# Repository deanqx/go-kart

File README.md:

# JCS-BK_1091_GO-KART_Blinker_Lenkrad_Anzeige

Die gesamte Dokumentation befindet sich unter `docs/pdf/JCS-BK_1091_GO-KART_Blinker_Lenkrad_Anzeige_Dokumentation_DeanS.pdf` gefunden werden.

# Abstract

For several years, students at the technical high school have been working on upgrading a go-kart by
integrating systems typically found in modern cars. The individual modules communicate via a CAN
bus network, similar to that used in real vehicles. Two microcontrollers from the AVR family are used
throughout the system. The task is devided into multiple projects − one for each student.
This document describes the development of the light modules and the cockpit module. There is also a
video showcasing the development. The lighting system consists of four modules, one for each corner
of the vehicle. The two front modules support upper beam, lower beam, and daytime running lights,
while the two rear modules provide tail, brake, and reverse lights.
The cockpit module includes a display, a horn, and several buttons mounted on the steering wheel. It
serves as the central interface between the driver and the vehicle systems. The display presents
information such as speed, battery charge, current gear, light status, and other relevant data. Using the
steering wheel buttons and switches, the driver can control things like the driving direction, light
mode, blinker direction, horn and gear.
All required tasks of this project were successfully completed. The service provider (TIO) did not
finish the Java-based frontend; however, the serial communication interface has already been
implemented. Since the other projects have not yet integrated CAN bus communication into their
modules, communication between the cockpit and the other systems is currently not possible. In
addition, a 3D-printed case for the display and caps for the buttons could be developed in the future.

# Kurzfassung

Seit mehreren Jahren arbeiten Schüler der gymnasialen Oberstufe Bereich Technik daran, ein Go-Kart
durch die Integration von Systemen, die typischerweise in modernen Autos zu finden sind,
aufzurüsten. Die einzelnen Module kommunizieren über CAN-Bus, ähnlich wie es in echten
Fahrzeugen verwendet wird. Im gesamten System kommen zwei Mikrocontroller aus der AVR-Familie
zum Einsatz. Die Aufgabe ist in mehrere Projekte unterteilt – eines für jeden Schüler.
Dieses Dokument beschreibt die Entwicklung der Lichtanlage, des Lenkrads und der Tachoanzeige.
Des weiteren gibt es ein Video in dem die Entwicklung gezeigt wird. Die Lichtanlage besteht aus vier
Modulen, eines für jede Ecke des Fahrzeugs. Die beiden vorderen Module unterstützen Fernlicht,
Abblendlicht und Tagfahrlicht, während die beiden hinteren Module Rücklicht, Bremslicht und
Rückfahrlicht liefern.
Das Cockpitmodul umfasst ein Display, eine Hupe und mehrere am Lenkrad angebrachte Taster. Es
dient als zentrale Schnittstelle zwischen dem Fahrer und den Fahrzeugsystemen. Das Display zeigt
Informationen wie Geschwindigkeit, Batterieladestand, aktueller Gang, Lichtstatus und andere
relevante Daten an. Mit den Tasten und Schaltern am Lenkrad kann der Fahrer beispielsweise die
Fahrtrichtung, den Lichtmodus, die Blinkerrichtung, die Hupe und den Gang steuern.
Alle gegebenen Aufgaben dieses Projekts wurden erfolgreich abgeschlossen. Der Dienstleister (TIO)
hat das Java-basierte Frontend nicht fertiggestellt, jedoch wurde die serielle Schnittstelle bereits
implementiert. Da die anderen Projekte die CAN-Bus-Kommunikation noch nicht in ihre Module
integriert haben, ist eine Kommunikation zwischen dem Cockpit und den anderen Systemen derzeit
nicht möglich. Darüber hinaus könnte in Zukunft ein 3D-gedrucktes Gehäuse für das Cockpit und
Kappen für die Lenkrad-Taster entwickelt werden.

# Credits

Dieses Projekt verwendet AVR-Bibliotheken, darunter:

- Eine verbesserte Version von [dergraaf/avr-can-lib](https://github.com/dergraaf/avr-can-lib)
  welche auf den ATmega16M1 angepasst wurde.
- USART Bibliothek [jnk0le/AVR-UART-lib](https://github.com/jnk0le/AVR-UART-lib)

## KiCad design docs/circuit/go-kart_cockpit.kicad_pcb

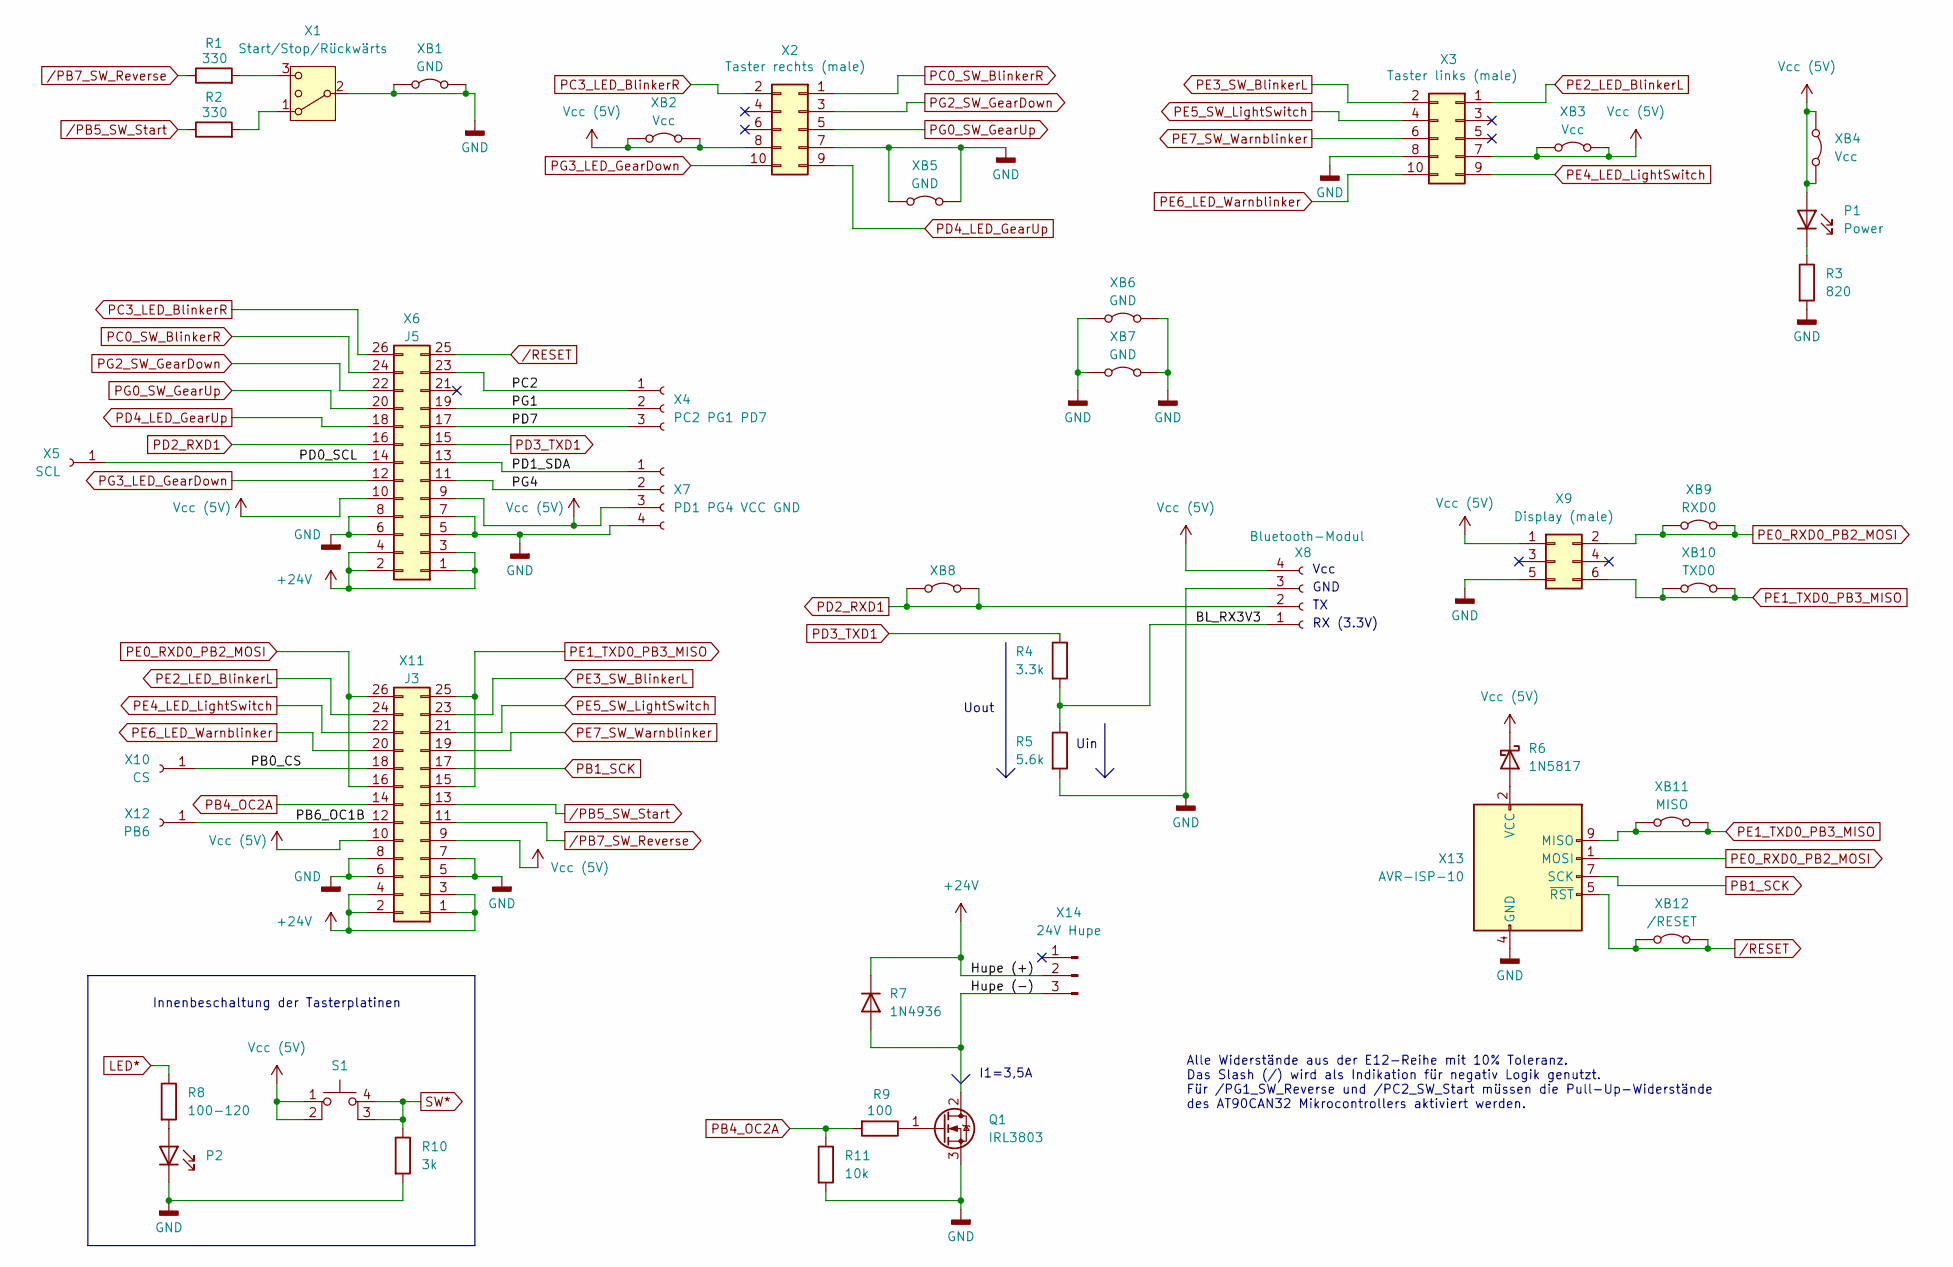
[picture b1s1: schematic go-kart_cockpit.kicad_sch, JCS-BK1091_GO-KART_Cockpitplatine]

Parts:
P1, P2: Power; LED_D3.0mm_Horizontal_O1.27mm_Z6.0mm
Q1: IRL3803; TO-220F-3_Horizontal_TabDown
R1, R2: 330; R_Axial_DIN0207_L6.3mm_D2.5mm_P10.16mm_Horizontal
R3: 820; R_Axial_DIN0309_L9.0mm_D3.2mm_P12.70mm_Horizontal
R4: 3.3k; R_Axial_DIN0207_L6.3mm_D2.5mm_P10.16mm_Horizontal
R5: 5.6k; R_Axial_DIN0207_L6.3mm_D2.5mm_P10.16mm_Horizontal
R6: 1N5817; D_DO-41_SOD81_P10.16mm_Horizontal
R7: 1N4936; D_DO-41_SOD81_P10.16mm_Horizontal
R8: 100-120
R9: 100; R_Axial_DIN0207_L6.3mm_D2.5mm_P7.62mm_Horizontal
R10: 3k
R11: 10k; R_Axial_DIN0207_L6.3mm_D2.5mm_P7.62mm_Horizontal
S1: SW_MEC_5E
X1: Start/Stop/Rückwärts; PhoenixContact_MC_1,5_3-G-5.08_1x03_P5.08mm_Horizontal
X2: Taster rechts (male); IDC-Header_2x05_P2.54mm_Horizontal
X3: Taster links (male); IDC-Header_2x05_P2.54mm_Horizontal
X4: PC2 PG1 PD7; PinSocket_1x03_P2.54mm_Vertical
X5: SCL; PinSocket_1x01_P2.54mm_Vertical
X6: J5; PinSocket_2x13_P2.54mm_Vertical
X7: PD1 PG4 VCC GND; PinSocket_1x04_P2.54mm_Vertical
X8: Bluetooth-Modul; PinSocket_1x04_P2.54mm_Horizontal
X9: Display (male); IDC-Header_2x03_P2.54mm_Horizontal
X10: CS; PinSocket_1x01_P2.54mm_Vertical
X11: J3; PinSocket_2x13_P2.54mm_Vertical
X12: PB6; PinSocket_1x01_P2.54mm_Vertical
X13: AVR-ISP-10; IDC-Header_2x05_P2.54mm_Horizontal
X14: 24V Hupe; PhoenixContact_MC_1,5_3-G-5.08_1x03_P5.08mm_Horizontal
XB1, XB6: GND; R_Axial_DIN0207_L6.3mm_D2.5mm_P10.16mm_Horizontal
XB2, XB3: Vcc; R_Axial_DIN0207_L6.3mm_D2.5mm_P10.16mm_Horizontal
XB4: Vcc; R_Axial_DIN0207_L6.3mm_D2.5mm_P7.62mm_Horizontal
XB5: GND; R_Axial_DIN0207_L6.3mm_D2.5mm_P15.24mm_Horizontal
XB7: GND; R_Axial_DIN0207_L6.3mm_D2.5mm_P7.62mm_Horizontal
XB8: R_Axial_DIN0207_L6.3mm_D2.5mm_P15.24mm_Horizontal
XB9: RXD0; R_Axial_DIN0207_L6.3mm_D2.5mm_P10.16mm_Horizontal
XB10: TXD0; R_Axial_DIN0207_L6.3mm_D2.5mm_P10.16mm_Horizontal
XB11: MISO; TestPoint_2Pads_Pitch5.08mm_Drill1.3mm
XB12: /RESET; R_Axial_DIN0207_L6.3mm_D2.5mm_P15.24mm_Horizontal

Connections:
+24V: R7.1 (K), X6.1, X6.2, X6.3, X6.4, X11.1, X11.2, X11.3, X11.4, X14.2
/BL_RX3V3: R4.2, R5.1, X8.1
/Hupe (-): Q1.2 (D), R7.2 (A), X14.3
/PB0_CS: X10.1, X11.18
/PB6_OC1B: X11.12, X12.1
/PC2: X4.1, X6.23
/PD0_SCL: X5.1, X6.14
/PD1_SDA: X6.13, X7.1
/PD7: X4.3, X6.17
/PG1: X4.2, X6.19
/PG4: X6.11, X7.2
GND: P2.1 (K), Q1.3 (S), R3.2, R5.2, R10.2, R11.2, X1.2 (3), X2.7, X3.8, X6.5, X6.6, X6.7, X6.8, X7.4, X8.3, X9.5, X11.5, X11.6, X11.7, X11.8, X13.4 (GND), X13.6 (GND), X13.8 (GND), X13.10 (GND), XB1.1 (A), XB1.2 (B), XB5.1 (A), XB5.2 (B), XB6.1 (A), XB6.2 (B), XB7.1 (A), XB7.2 (B)
unnamed: P1.1 (K), R3.1
unnamed: P2.2 (A), R8.2
unnamed: Q1.1 (G), R9.1
unnamed: R2.2, X1.1
unnamed: R6.2 (A), X13.2 (VCC)
unnamed: R10.1, S1.3 (K), S1.4 (A)
unnamed: R1.2, X1.3 (4)
PB1_SCK: X11.17, X13.7 (SCK)
PB4_OC2A: R9.2, R11.1, X11.14
PC0_SW_BlinkerR: X2.1, X6.24
PC3_LED_BlinkerR: X2.2, X6.26
PD2_RXD1: X6.16, X8.2, XB8.1 (A), XB8.2 (B)
PD3_TXD1: R4.1, X6.15
PD4_LED_GearUp: X2.9, X6.18
PE0_RXD0_PB2_MOSI: X9.2, X11.16, X11.26, X13.1 (MOSI), XB9.1 (A), XB9.2 (B)
PE1_TXD0_PB3_MISO: X9.6, X11.15, X11.25, X13.9 (MISO), XB10.1 (A), XB10.2 (B), XB11.1 (A), XB11.2 (B)
PE2_LED_BlinkerL: X3.1, X11.24
PE3_SW_BlinkerL: X3.2, X11.23
PE4_LED_LightSwitch: X3.9, X11.22
PE5_SW_LightSwitch: X3.4, X11.21
PE6_LED_Warnblinker: X3.10, X11.20
PE7_SW_Warnblinker: X3.6, X11.19
PG0_SW_GearUp: X2.5, X6.20
PG2_SW_GearDown: X2.3, X6.22
PG3_LED_GearDown: X2.10, X6.12
Vcc (5V): P1.2 (A), R6.1 (K), S1.1, S1.2, X2.8, X3.7, X6.9, X6.10, X7.3, X8.4, X9.1, X11.9, X11.10, XB2.1 (A), XB2.2 (B), XB3.1 (A), XB3.2 (B), XB4.1 (A), XB4.2 (B)
/PB5_SW_Start: R2.1, X11.13
/PB7_SW_Reverse: R1.1, X11.11
/RESET: X6.25, X13.5 (~RST), XB12.1 (A), XB12.2 (B)

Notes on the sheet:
Innenbeschaltung der Tasterplatinen
Uin
Alle Widerstände aus der E12-Reihe mit 10% Toleranz. Das Slash (/) wird als Indikation für negativ Logik genutzt. Für /PG1_SW_Reverse und /PC2_SW_Start müssen die Pull-Up-Widerstände des AT90CAN32 Mikrocontrollers aktiviert werden.
I1=3,5A
GND
Vcc
Uout
RX (3.3V)

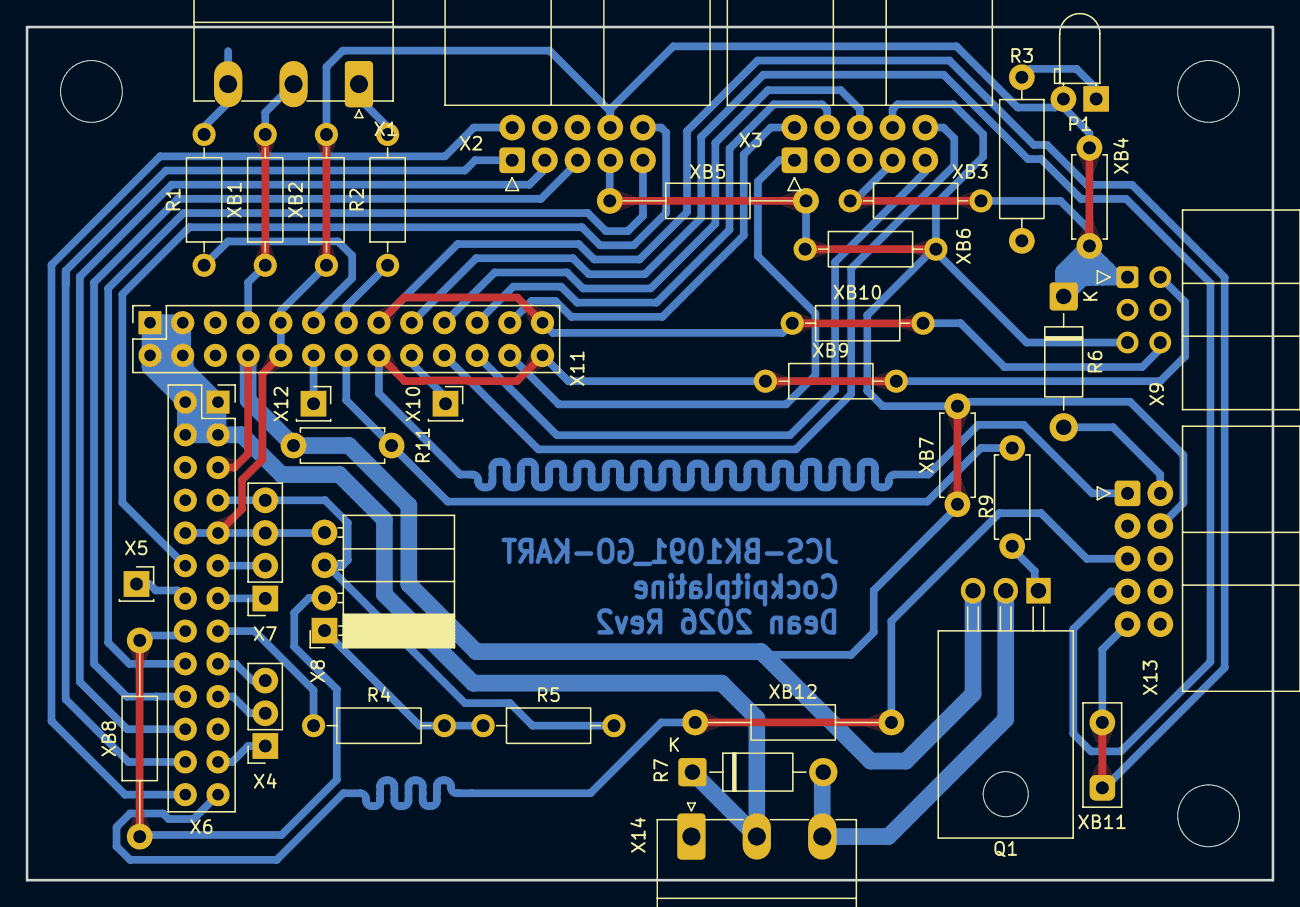
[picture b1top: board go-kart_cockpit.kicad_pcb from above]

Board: 2 copper layers, 96.8 x 66.2 mm, 37 parts (0 on the bottom side), 39 nets.

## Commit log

2025-09-08 feat: setup docs format
2025-09-11 docs: rename docs to documentation
2025-09-12 feat(pflichtenheft): add first page and rough layout
2025-09-22 feat: insert lastenheft into pflichtenheft
2025-09-22 feat: add projects of predecessors, add goals and existing things
2025-09-25 fix: link and Deckblatt
2025-09-25 fix: remove lock
2025-09-25 feat(pflichtenheft): Terminplan eingefügt
2025-09-26 feat(pflichtenheft): change structure and insert missing tables
2025-09-26 feat(pflichtenheft): insert title image
2025-09-26 feat(pflichtenheft): first Aufgabenstellung
2025-09-26 feat: improve overall and Aufgabenstellung
2025-09-27 feat: Aufgabenstellung und alte Projekte
2025-09-28 docs(Plichtenheft): erste Abgabe ohne Überarbeitung
2025-09-28 docs(Plichtenheft): erste Abgabe
2025-09-28 docs(Plichtenheft): update all references
2025-10-08 feat: Pflichtenheft Korrektur
2025-11-09 feat: bluetooth module
2025-11-10 feat: test display
2025-11-11 feat: add Spannungsregler
2025-11-12 feat: use block text and hint where to find AT90CAN docs
2025-11-13 feat: trying to upload to AT90CAN32
2025-11-14 feat: blink test for AT90CAN, docs are not complete
2025-11-15 docs: permissions for USB, improved docs for first test with AT90CAN
2025-11-30 feat: final touches on documentation for draft 1
2025-11-30 feat: adjust for Zwischenstand submission
2026-01-19 feat: cockpit display library (untested)
2026-01-20 docs: Schaltplan für Bluetooth, cmake Erklärung, CAN-Sniffing
2026-01-22 docs: images from old projects are not allowed
2026-01-22 docs: general improvements
2026-01-22 docs: sort alte projekte in descending order
2026-01-22 docs: abstract, cockpit-display, oled-display, general improvements
2026-01-23 feat: blink test for ATmega16M1 (blinker module)
2026-01-23 feat: add can library
2026-01-23 docs: cockpit display commands, basic mcu introduction and more
2026-01-23 docs: draft 2 documentation, add Tagesziele
2026-01-24 feat: test LEDs of blinker module
2026-01-24 WIP(blinker): set up can bus
2026-01-27 WIP: trying to use USART on AT90CAN
2026-01-28 build: improve cmake target selection
2026-01-28 fix: usart library for AT90CAN32
2026-01-28 feat: test cockpit display with AT90CAN32, fix cockpit display library
2026-01-29 docs: USB Rechte kurz beschrieben
2026-01-29 docs: small improvement in error message
2026-01-29 WIP: testing CAN on AT90CAN
2026-01-29 WIP: transmitting working, still cant receive
2026-01-30 feat: successful CAN-Bus test with AT90CAN
2026-02-01 feat: successful CAN-Bus echo test with ATmega16M1
2026-02-01 feat: blinker controller
2026-02-03 docs: add Quellenverzeichnis, improve Signaltime diagram
2026-02-04 refactor: move can library to forked repo
2026-02-04 feat: (untested) add commands, add UART for ATmega16M1
2026-02-09 style: reformat uart_AM16M1.h
2026-02-09 feat: control blinker with UART (with bug)
2026-02-09 feat: PWM for break and backlight, send periodically state over CAN
2026-02-10 fix: PWM was not fast enough, Blinker-Modul is working
2026-02-10 build: update cmake and refactore code to support multiple blinker compile targets
2026-02-10 docs: create CAN ID table
2026-02-11 fix: do not send light state if UART command failed
2026-02-11 feat: CAN_ID table first version
2026-02-12 feat(blinker): use correct CAN IDs and state message
2026-02-12 fix(blinker): lower light is turned off by blinker code
2026-02-12 feat: circuit for switches
2026-02-12 WIP: planning cockpit pins
2026-02-12 WIP: circuit
2026-02-12 feat(circuit): use internal pull up resistors
2026-02-13 feat: circuit before rework with larger plate
2026-02-15 feat: planned connections to MCU
2026-02-15 feat: allow disabling upper light
2026-02-15 feat: set pins in code
2026-02-15 feat: cockpit test code (untested)
2026-02-15 feat: TI_Zwischenabgabe
2026-02-16 feat: first sketch of PCB
2026-02-16 feat(circuit): fixed DRC
2026-02-16 feat(circuit): final touches
2026-02-16 feat(PCB): checklist and LED calculation
2026-02-16 feat(PCB): add pull down resistor in preperation for FET
2026-02-16 feat(PCB): add teardrops
2026-02-17 feat(PCB): improve connectors and position
2026-02-17 feat(PCB): replace TIP120 with MOSFET
2026-02-20 feat: cleanup Tasterinnenbeschaltung for presentation
2026-03-02 feat: rework of PCB, fix wrong connection
2026-03-03 feat(PCB): replace 100 ohm preresistors with 330
2026-03-03 fix(PCB): green connector drill holes are too small, built PCB
2026-03-03 feat(cockpit): update hal to reflect PCB change
2026-03-04 WIP(cockpit): test PCB
2026-03-05 feat(cockpit): test program for horn
2026-03-05 feat(cockpit): test all switches
2026-03-05 feat(cockpit): read switches with interrupt
2026-03-05 feat(cockpit): toggleable buttons
2026-03-05 feat(cockpit): only update if something has changed
2026-03-05 feat(cockpit): control blinker with can bus (untested)
2026-03-06 fix(PCB): ISP is actually connected to UART0 instead of SPI
2026-03-07 docs: rename can_ids to can_protokoll
2026-03-07 docs: inserted PCB graphics, general improvements
2026-03-07 docs: add communication diagram, add finished products
2026-03-07 feat(blinker): use more accurate timer values
2026-03-07 docs: abstract
2026-03-07 docs: add video hint to abstract
2026-03-07 docs: fix wrong image aspect ratio
2026-03-08 docs: add communication diagram
2026-03-08 feat(cockpit): remove STB-style library, split into .c and .h files
2026-03-10 docs: add digital timing diagram
2026-03-12 feat: update program for blinkers
2026-03-12 docs: update comment
2026-03-12 docs: add suggestions from schmidt
2026-03-12 docs: prepared working time calculation
2026-03-12 docs: improvements
2026-03-12 docs: rename PDFs
2026-03-13 docs: update Terminplan
2026-03-13 docs: add missing images
2026-03-13 docs: final documentation
2026-03-17 fix(cockpit): bug with setting blinker, improve debug messages
2026-03-19 feat: turn red light on when low beam is enabled
2026-03-19 refactor(blinker): rename uart library
2026-03-20 feat(cockpit): add warnblinker functionality
2026-03-20 fix(cockpit): turning off warnblinker does not deactivate light, more time between button reading
2026-03-20 refactor(cockpit): rename send function, add hal comment
2026-03-20 docs: add github link in readme
2026-03-22 fix(blinker): add volatile to variables which are modified by interrupt
2026-03-22 feat(blinker): UART with buffer (interrupt)
2026-03-22 docs: expand README with project abstract and summary
